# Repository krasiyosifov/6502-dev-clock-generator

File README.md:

# dev-clock-generator
A clock generator, which can be used to clock 6502 based homebrew computer or similar

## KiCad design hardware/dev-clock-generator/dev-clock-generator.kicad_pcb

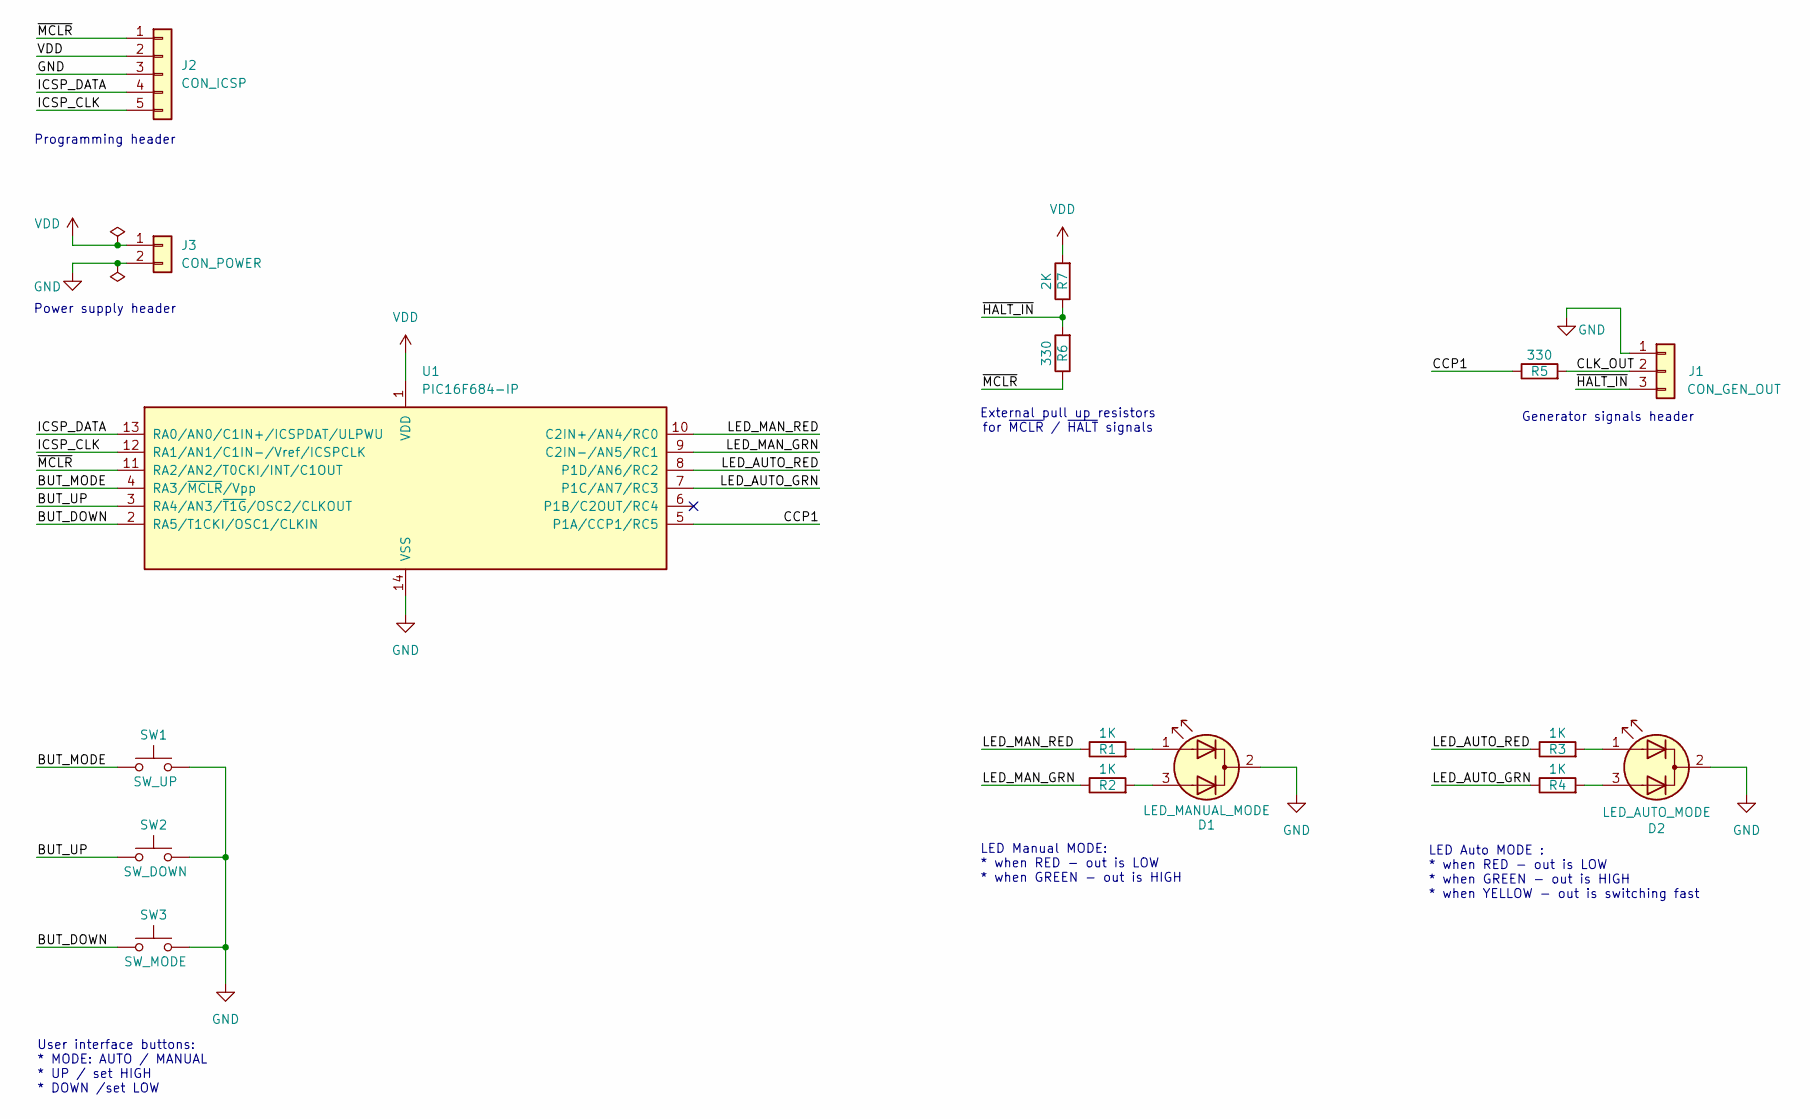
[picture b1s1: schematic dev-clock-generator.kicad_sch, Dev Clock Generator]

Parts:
D1: LED_MANUAL_MODE; LED_D5.0mm-3
D2: LED_AUTO_MODE; LED_D5.0mm-3
J1: CON_GEN_OUT; PinHeader_1x02_P2.54mm_Vertical
J2: CON_ICSP; PinHeader_1x05_P2.54mm_Vertical
J3: CON_POWER; PinSocket_1x02_P2.54mm_Vertical
R1, R2, R3, R4: 1K; R_Axial_DIN0207_L6.3mm_D2.5mm_P10.16mm_Horizontal
R5, R6: 330; R_Axial_DIN0207_L6.3mm_D2.5mm_P10.16mm_Horizontal
R7: 2K; R_Axial_DIN0207_L6.3mm_D2.5mm_P10.16mm_Horizontal
SW1: SW_UP; SW_PUSH_6mm_H5mm
SW2: SW_DOWN; SW_PUSH_6mm_H5mm
SW3: SW_MODE; SW_PUSH_6mm_H5mm
U1: PIC16F684-IP; DIP-14_W7.62mm_Socket

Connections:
/BUT_DOWN: SW3.1, U1.2 (RA5/T1CKI/OSC1/CLKIN)
/BUT_MODE: SW1.1, U1.4 (RA3/~MCLR/Vpp)
/BUT_UP: SW2.1, U1.3 (RA4/AN3/~T1G/OSC2/CLKOUT)
/CCP1: R5.1, U1.5 (P1A/CCP1/RC5)
/CLK_OUT: J1.2, R5.2
/ICSP_CLK: J2.5, U1.12 (RA1/AN1/C1IN-/Vref/ICSPCLK)
/ICSP_DATA: J2.4, U1.13 (RA0/AN0/C1IN+/ICSPDAT/ULPWU)
/LED_AUTO_GRN: R4.1, U1.7 (P1C/AN7/RC3)
/LED_AUTO_RED: R3.1, U1.8 (P1D/AN6/RC2)
/LED_MAN_GRN: R2.1, U1.9 (C2IN-/AN5/RC1)
/LED_MAN_RED: R1.1, U1.10 (C2IN+/AN4/RC0)
/~HALT_IN: J1.3, R6.2, R7.1
/~MCLR: J2.1, R6.1, U1.11 (RA2/AN2/T0CKI/INT/C1OUT)
GND: D1.2 (K), D2.2 (K), J1.1, J2.3, J3.2, SW1.2, SW2.2, SW3.2, U1.14 (VSS)
unnamed: D1.1 (A1), R1.2
unnamed: D1.3 (A2), R2.2
unnamed: D2.1 (A1), R3.2
unnamed: D2.3 (A2), R4.2
VDD: J2.2, J3.1, R7.2, U1.1 (VDD)

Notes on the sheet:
Programming header
LED Manual MODE: * when RED - out is LOW * when GREEN - out is HIGH
Power supply header
Generator signals header
External pull up resistors for ~{MCLR} / ~{HALT} signals
User interface buttons: * MODE: AUTO / MANUAL * UP / set HIGH * DOWN /set LOW
LED Auto MODE : * when RED - out is LOW * when GREEN - out is HIGH * when YELLOW - out is switching fast

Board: 2 copper layers, 16 parts (0 on the bottom side), 19 nets, no tracks yet.

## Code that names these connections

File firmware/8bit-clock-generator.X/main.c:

/**
 * File:   main.c
 * Author: krasi.yosifov@gmail.com
 *
 * Created on 09.12.2024
 *
 * ****************************
 * Development Clock Generator
 * ****************************
 *
 * This project implements a clock generator with two operational modes:
 * Manual Mode and Auto Mode, controlled via the "mode" button.
 *
 * Behavior:
 * - Manual Mode:
 *   - "+/high" button: Sets the output clock HIGH.
 *   - "-/low" button: Sets the output clock LOW.
 *   - If the output clock is already in the desired state, clicking the respective button toggles
 *     the clock state momentarily before returning to the desired level.
 *
 * - Auto Mode:
 *   - "+/high" button: Increases the output frequency to the next higher standard frequency.
 *   - "-/low" button: Decreases the output frequency to the next lower standard frequency.
 *   - Standard frequencies:
 *          1Hz, 4Hz, 20Hz, 100Hz, 500Hz,
 *          2KHz, 10KHz, 50KHz, 200KHz,
 *          1MHz, 2MHz.
 *
 * Additional Features:
 * - Halt Signal: An active LOW input halts the generator and sets the clock output to manual LOW state.
 *
 * Microcontroller IC: PIC16F684 (14 pin PDIP 8-bit microcontroller)
 * Documentation: https://ww1.microchip.com/downloads/en/DeviceDoc/41202F-print.pdf
 *
 * Developed using:
 *      MPLAB X IDE: v6.20
 *      Compiler: XC8 v2.36
 *
 * Hardware connections
 * PIN 1    VDD - 5V
 * PIN 2    RA5 - Button down           (internal pullup)
 * PIN 3    RA4 - Button up             (internal pullup)
 * PIN 4    RA3 - Button MODE           (external pullup)
 * PIN 5    RC5 - CLK out
 * PIN 6    RC4 -
 * PIN 7    RC3 - LED Auto (green)
 * PIN 8    RC2 - LED Auto (red)
 * PIN 9    RC1 - LED Manual (green)
 * PIN 10   RC0 - LED Manual (red)
 * PIN 11   RA2 - nHALT input signal    (internal pullup)
 * PIN 12   RA1 - ICSP
 * PIN 13   RA0 - ICSP
 * PIN 14   VSS - GND
 *
 */


// PIC16F684 CONFIG
#pragma config FOSC = INTOSCIO  // Oscillator Selection bits (INTOSCIO oscillator: I/O function on RA4/OSC2/CLKOUT pin, I/O function on RA5/OSC1/CLKIN)
#pragma config WDTE = OFF       // Watchdog Timer Enable bit (WDT disabled)
#pragma config PWRTE = ON       // Power-up Timer Enable bit (PWRT enabled)
#pragma config MCLRE = OFF      // MCLR Pin Function Select bit (MCLR pin function is digital input, MCLR internally tied to VDD)
#pragma config CP = OFF         // Code Protection bit (Program memory code protection is disabled)
#pragma config CPD = OFF        // Data Code Protection bit (Data memory code protection is disabled)
#pragma config BOREN = ON       // Brown Out Detect (BOR enabled)
#pragma config IESO = OFF       // Internal External Switchover bit (Internal External Switchover mode is disabled)
#pragma config FCMEN = OFF      // Fail-Safe Clock Monitor Enabled bit (Fail-Safe Clock Monitor is enabled)


#include <xc.h>
#include "buttons.h"
#include "hardware.h"
#include "interrupts.h"
#include "leds.h"
#include "generator.h"


/**
 * Main function
 */
void main(void)
{
    buttons_state_t * buttonsState;

    harware_init();             // initialize hardware
    generator_init();           // initialize generator
    ei();                       // enable all interrupts

    // loop forever
    while (1) {
        // update timer 1 overflow event
        if (interrupt_flags.timer1Overflow) {
            if (interrupt_flags.stopGenerator == 0) {
                // check that the stop generator signal is not active
                generator_timer1Callback();
            }
            interrupt_flags.timer1Overflow = 0;
        }

        // update application state
        if (interrupt_flags.stopGenerator) {
            interrupt_flags.stopGenerator = 0;
            generator_stop();
        }

        // read buttons
        if (interrupt_flags.readButtons) {
            interrupt_flags.readButtons = 0;

            // update individual buttons states
            buttons_updateButtonState(BUTTON_UP, BUTTON_UP_PIN);
            buttons_updateButtonState(BUTTON_DOWN, BUTTON_DOWN_PIN);
            buttons_updateButtonState(BUTTON_MODE, BUTTON_MODE_PIN);

            // read buttons calculated state
            buttonsState = buttons_getState();

            // handle button UP
            if (buttonsState->buttonUp.pressed) {
                buttonsState->buttonUp.pressed = 0;
                if (generator_getMode() == GEN_MODE_MANUAL) {
                    generator_setManualState(GEN_STATE_MANUAL_HIGH);
                } else {
                    generator_increaseFrequency();
                }
            }

            // handle button DOWN
            if (buttonsState->buttonDown.pressed) {
                buttonsState->buttonDown.pressed = 0;
                if (generator_getMode() == GEN_MODE_MANUAL) {
                    generator_setManualState(GEN_STATE_MANUAL_LOW);
                } else {
                    generator_decreaseFrequency();
                }
            }

            // handle button MODE
            if (buttonsState->buttonMode.pressed) {
                buttonsState->buttonMode.pressed = 0;
                generator_toggleMode();
            }
        }
    }
}

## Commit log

2024-12-12 software working state
2024-12-12 code cleanup
2024-12-13 swapped button pins
2024-12-13 schematic diagram
2024-12-13 updated gitignore
